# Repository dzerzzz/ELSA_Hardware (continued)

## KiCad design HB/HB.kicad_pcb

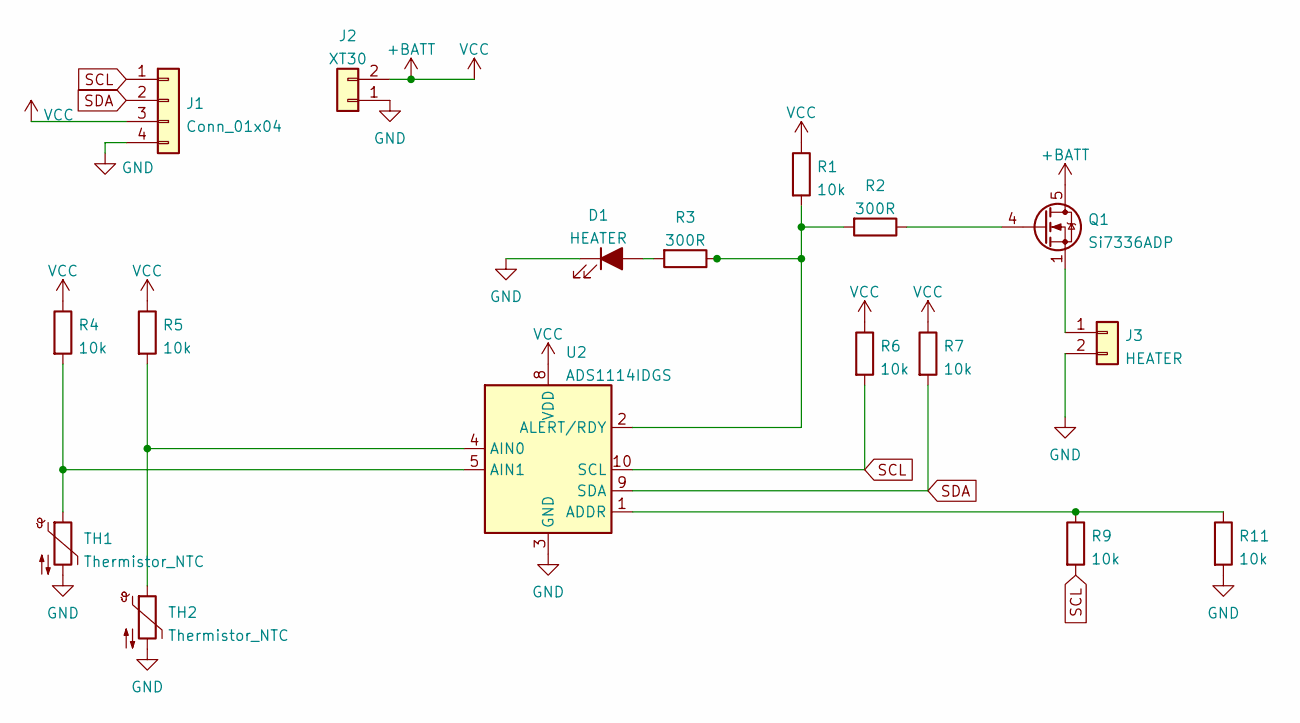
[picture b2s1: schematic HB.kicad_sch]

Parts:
D1: HEATER; LED_0603_1608Metric
J1: Conn_01x04; NS-Tech_Grove_1x04_P2mm_Vertical
J2: XT30; AMASS_XT30U-F_1x02_P5.0mm_Vertical
J3: HEATER
Q1: Si7336ADP; PowerPAK_SO-8_Single
R1, R4, R5, R6, R7, R9, R11: 10k; R_0603_1608Metric
R2, R3: 300R; R_0603_1608Metric
TH1, TH2: Thermistor_NTC; R_0402_1005Metric
U2: ADS1114IDGS; TSSOP-10_3x3mm_P0.5mm

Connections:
+BATT: J1.3, J2.2, Q1.5 (D), R1.1, R4.1, R5.1, R6.1, R7.1, U2.8 (VDD)
GND: D1.1 (K), J1.4, J2.1, J3.2, R11.2, TH1.2, TH2.2, U2.3 (GND); also elsewhere on the board
unnamed: D1.2 (A), R3.2
unnamed: J3.1, Q1.1 (S), Q1.2 (S), Q1.3 (S)
unnamed: Q1.4 (G), R2.1
unnamed: R1.2, R2.2, R3.1, U2.2 (ALERT/RDY)
unnamed: R4.2, TH1.1, U2.5 (AIN1)
unnamed: R5.2, TH2.1, U2.4 (AIN0)
unnamed: R9.1, R11.1, U2.1 (ADDR)
SCL: J1.1, R6.2, R9.2, U2.10 (SCL)
SDA: J1.2, R7.2, U2.9 (SDA)

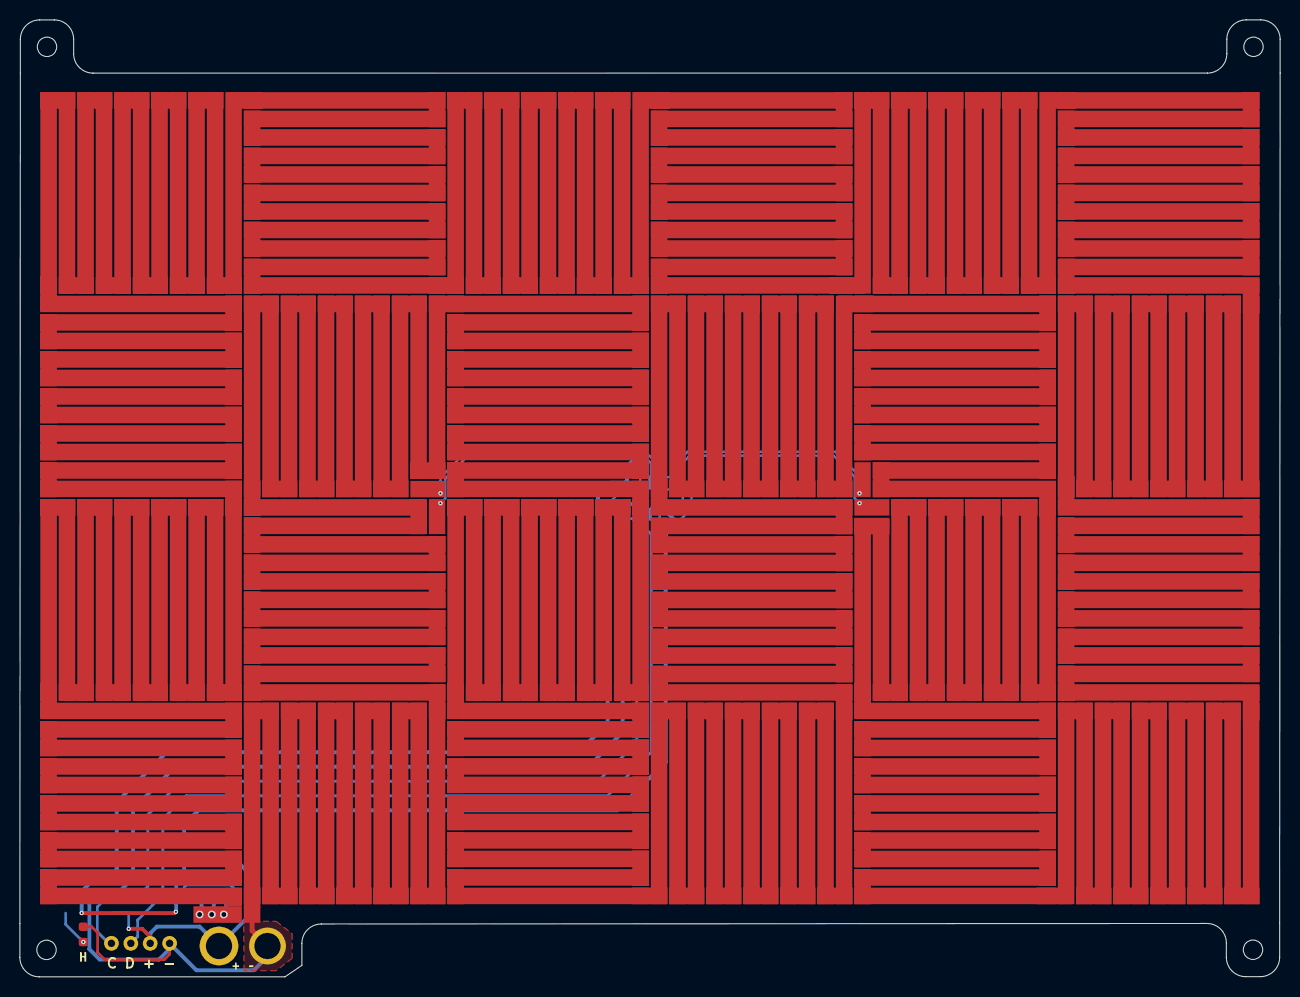
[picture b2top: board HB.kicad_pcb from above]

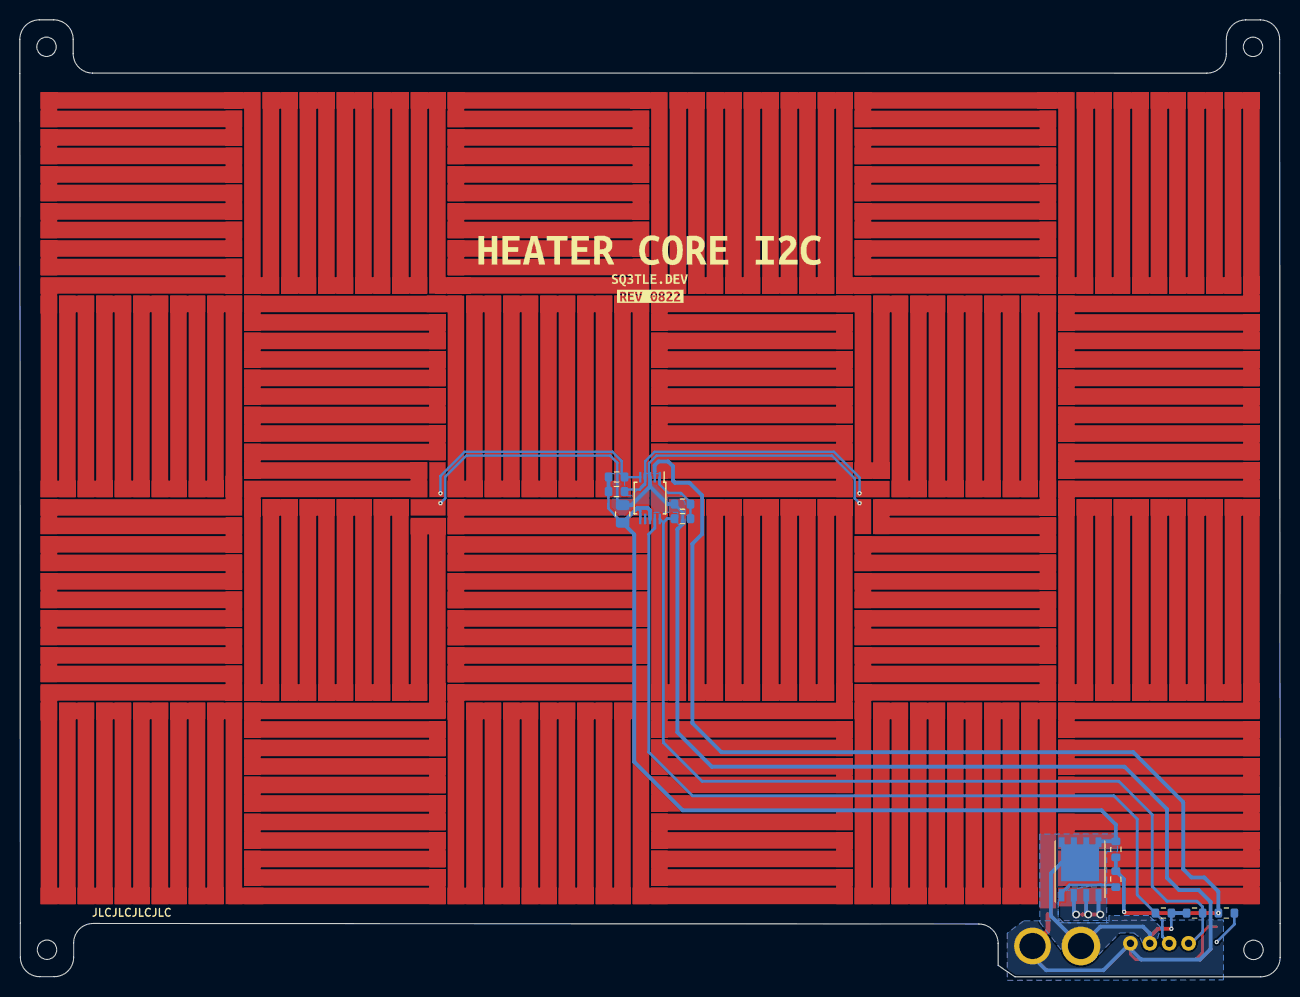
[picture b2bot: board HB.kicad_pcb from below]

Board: 2 copper layers, 130.1 x 98.8 mm, 23 parts (15 on the bottom side), 11 nets.

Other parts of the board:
C1: 10u; R_0805_2012Metric
kibuzzard-62FCEEC8: G***; kibuzzard-62FCEEC8
kibuzzard-62FCEF49: G***; kibuzzard-62FCEF49
kibuzzard-62FCEF83: G***; kibuzzard-62FCEF83
kibuzzard-62FCEFD6: G***; kibuzzard-62FCEFD6
kibuzzard-62FCF123: G***; kibuzzard-62FCF123

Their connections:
GND: C1.2; also elsewhere on the board

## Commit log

2024-01-16 Added EPS files
2024-01-16 Added PCS files
2024-01-16 Added KREWETACM4 firmware
2024-02-28 Added KREWETACM4 hardware
2024-10-06 updated hardware ELSA and HB
2024-10-06 updated KREWETA hardware
2024-10-08 deleted HB directory
